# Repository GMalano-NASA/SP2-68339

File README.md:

# SP2-68339
Single voltage alarm with set point  
Comparador Mod. CNEA K630  
Reemplazo del equipo Rochester 1214-P11  

## No fabricar como está.
Se necesitan verificar las dimensiones y ubicaciones de los componentes y conectores.  
Se replicó de acuerdo a las imágenes pero sin tener la placa disponible para el control dimensional.

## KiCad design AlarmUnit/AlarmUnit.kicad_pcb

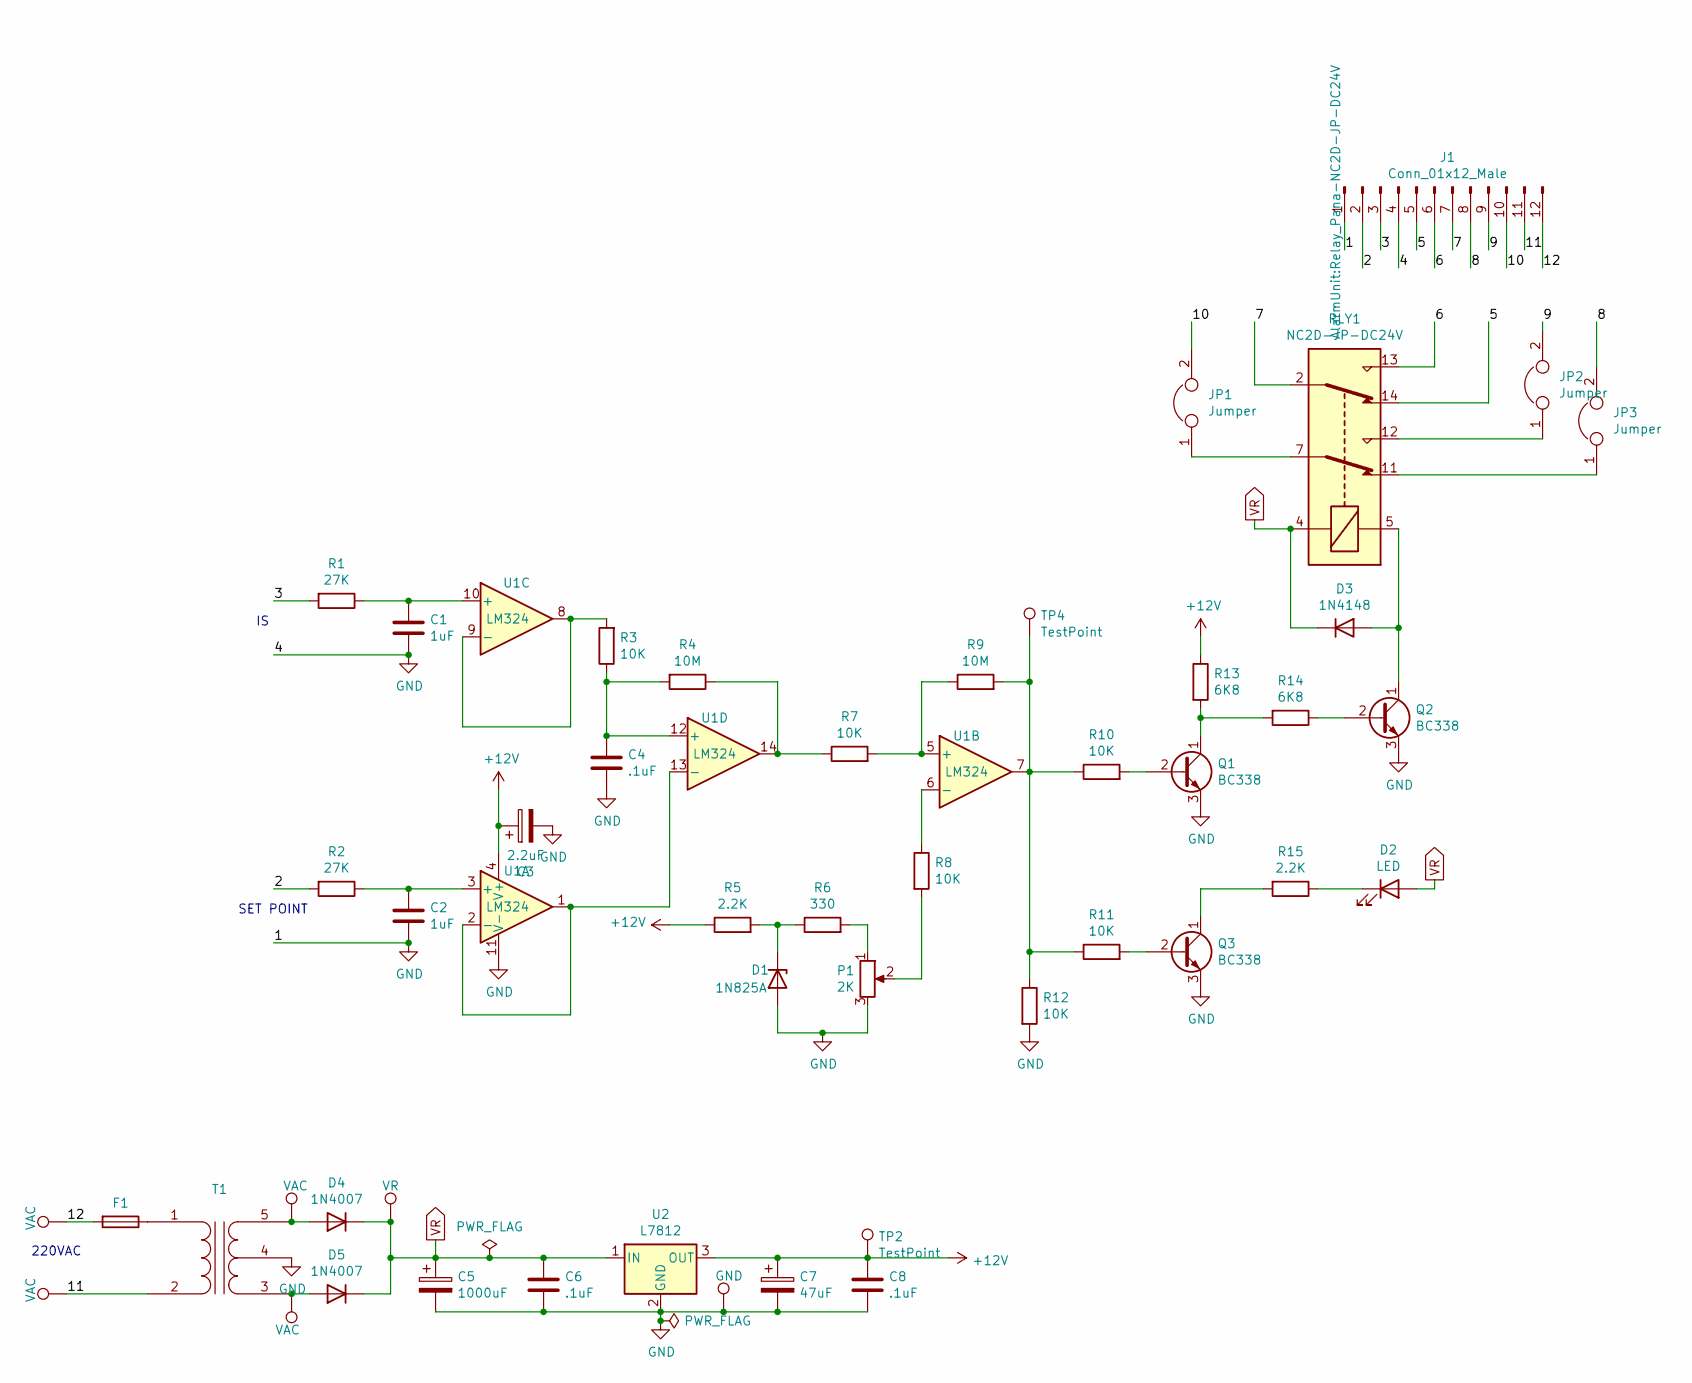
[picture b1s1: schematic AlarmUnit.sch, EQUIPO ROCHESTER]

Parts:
C1, C2: 1uF; CP_Radial_Tantal_D4.5mm_P2.50mm
C3: 2.2uF; CP_Radial_Tantal_D5.0mm_P2.50mm
C4, C6, C8: .1uF; C_Disc_D5.1mm_W3.2mm_P5.00mm
C5: 1000uF; CP_Axial_L38.0mm_D21.0mm_P44.00mm_Horizontal
C7: 47uF; CP_Radial_D5.0mm_P2.00mm
D1: 1N825A; D_DO-35_SOD27_P7.62mm_Horizontal
D2: LED; LED_D5.0mm_Horizontal_O6.35mm_Z9.0mm
D3: 1N4148; D_DO-35_SOD27_P7.62mm_Horizontal
D4, D5: 1N4007; D_DO-41_SOD81_P10.16mm_Horizontal
E2, E13: VAC; TestPoint_Loop_D1.80mm_Drill1.0mm_Beaded
F1: Fuse
GND1: GND; TestPoint_Loop_D1.80mm_Drill1.0mm_Beaded
J1: Conn_01x12_Male; MolexConnBarrierStrip12Pos-953mm
JP1, JP2, JP3: Jumper; WiredJumper
P1: 2K; Potentiometer_Bourns_3009Y_Horizontal
Q1, Q2, Q3: BC338; TO-92_Inline
R1, R2: 27K; R_Axial_DIN0207_L6.3mm_D2.5mm_P7.62mm_Horizontal
R3, R7, R8, R10, R11, R12: 10K; R_Axial_DIN0207_L6.3mm_D2.5mm_P7.62mm_Horizontal
R4, R9: 10M; R_Axial_DIN0207_L6.3mm_D2.5mm_P7.62mm_Horizontal
R5, R15: 2.2K; R_Axial_DIN0207_L6.3mm_D2.5mm_P7.62mm_Horizontal
R6: 330; R_Axial_DIN0207_L6.3mm_D2.5mm_P7.62mm_Horizontal
R13, R14: 6K8; R_Axial_DIN0207_L6.3mm_D2.5mm_P7.62mm_Horizontal
RLY1: NC2D-JP-DC24V; Relay_Pana-NC2D-JP-DC24V
T1: Transformer_1P_SS
TP2, TP4: TestPoint; TestPoint_Loop_D1.80mm_Drill1.0mm_Beaded
U1: LM324; DIP-14_W7.62mm
U2: L7812; TO-220-3_Horizontal_TabDown
VAC1, VAC2: VAC; TestPoint_THTPad_D2.5mm_Drill1.2mm
VR1: VR; TestPoint_Loop_D1.80mm_Drill1.0mm_Beaded

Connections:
+12V: C3.1, C7.1, C8.1, R5.1, R13.1, TP2.1, U1.4 (V+), U2.3 (OUT)
/2: J1.2, R2.2
/3: J1.3, R1.2
/5: J1.5, RLY1.14
/6: J1.6, RLY1.13
/7: J1.7, RLY1.2
/8: J1.8, JP3.2
/9: J1.9, JP2.2
/10: J1.10, JP1.2
/11: J1.11, T1.2 (AB), VAC2.1
/12: F1.2, J1.12, VAC1.1
GND: C1.2, C2.2, C3.2, C4.2, C5.2, C6.2, C7.2, C8.2, D1.2 (A), GND1.1, J1.1, J1.4, P1.3, Q1.3 (E), Q2.3 (E), Q3.3 (E), R12.2, T1.4 (SC), U1.11 (V-), U2.2 (GND)
unnamed: C1.1, R1.1, U1.10 (+)
unnamed: C2.1, R2.1, U1.3 (+)
unnamed: C4.1, R3.1, R4.2, U1.12 (+)
unnamed: D1.1 (K), R5.2, R6.1
unnamed: D2.1 (K), R15.1
unnamed: D3.2 (A), Q2.1 (C), RLY1.5
unnamed: D4.2 (A), E13.1, T1.5 (SB)
unnamed: D5.2 (A), E2.1, T1.3 (SA)
unnamed: F1.1, T1.1 (AA)
unnamed: JP1.1, RLY1.7
unnamed: JP2.1, RLY1.12
unnamed: JP3.1, RLY1.11
unnamed: P1.1, R6.2
unnamed: P1.2, R8.2
unnamed: Q1.1 (C), R13.2, R14.2
unnamed: Q1.2 (B), R10.2
unnamed: Q2.2 (B), R14.1
unnamed: Q3.1 (C), R15.2
unnamed: Q3.2 (B), R11.2
unnamed: R3.2, U1.8, U1.9 (-)
unnamed: R4.1, R7.1, U1.14
unnamed: R7.2, R9.1, U1.5 (+)
unnamed: R8.1, U1.6 (-)
unnamed: R9.2, R10.1, R11.1, R12.1, TP4.1, U1.7
unnamed: U1.1, U1.2 (-), U1.13 (-)
VR: C5.1, C6.1, D2.2 (A), D3.1 (K), D4.1 (K), D5.1 (K), RLY1.4, U2.1 (IN), VR1.1

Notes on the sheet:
SET POINT
220VAC

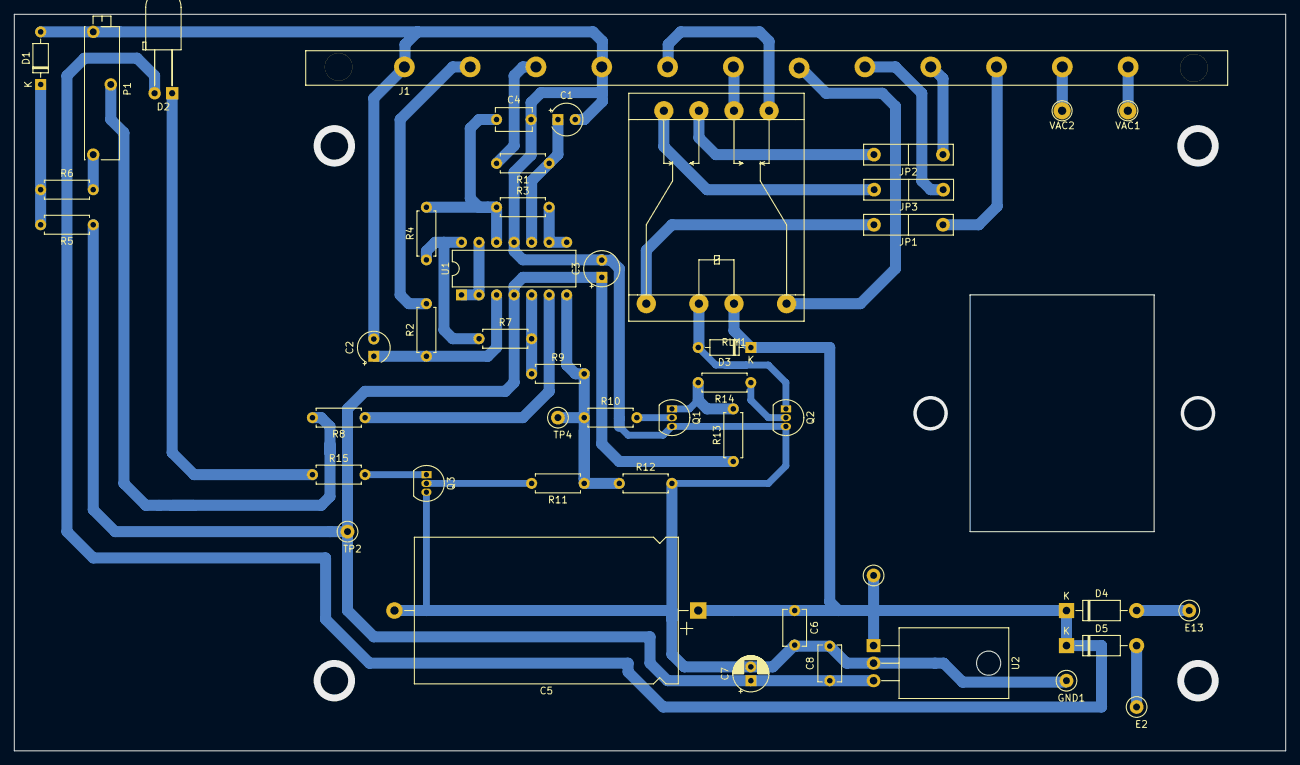
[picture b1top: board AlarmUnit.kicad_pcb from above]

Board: 2 copper layers, 184.2 x 106.7 mm, 47 parts (0 on the bottom side), 37 nets.

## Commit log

2023-08-07 ya algunos componentes distribuidos en la placa
2023-08-07 componentes distribuidos a ojo, verificar medidas
2023-08-09 avances en routeado
2023-08-10 ruteada placa completa
2023-08-11 algunos tweaks
